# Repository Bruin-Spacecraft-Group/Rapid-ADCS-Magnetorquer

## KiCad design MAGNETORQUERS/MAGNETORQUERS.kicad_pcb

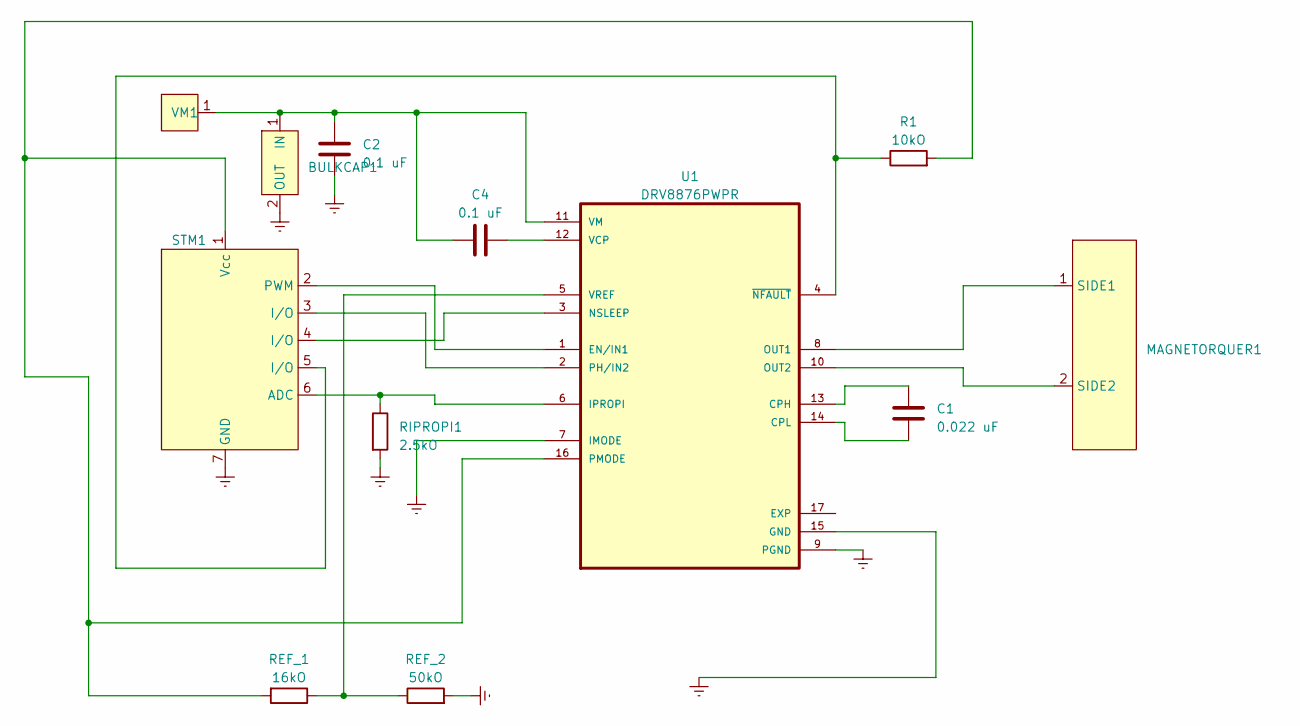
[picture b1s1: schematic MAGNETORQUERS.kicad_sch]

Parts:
BULKCAP1: PinHeader_1x02_P2.54mm_Vertical
C1: 0.022 uF; R_0603_1608Metric
C2, C4: 0.1 uF; R_0603_1608Metric
MAGNETORQUER1: PinHeader_1x02_P2.54mm_Vertical
R1: 10kO; R_0603_1608Metric
REF_1: 16kO; R_0603_1608Metric
REF_2: 50kO; R_0603_1608Metric
RIPROPI1: 2.5kO; R_0603_1608Metric
STM1: PinHeader_1x07_P2.54mm_Vertical
U1: DRV8876PWPR; IC_DRV8876PWPR; PARTREV E
VM1: PinHeader_1x01_P2.54mm_Vertical

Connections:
Earth: BULKCAP1.2 (OUT), C2.2, REF_2.2, RIPROPI1.2, STM1.7 (GND), U1.7 (IMODE), U1.9 (PGND), U1.15 (GND)
unnamed: BULKCAP1.1 (IN), C2.1, C4.1, U1.11 (VM), VM1.1
unnamed: MAGNETORQUER1.1 (SIDE1), U1.8 (OUT1)
unnamed: MAGNETORQUER1.2 (SIDE2), U1.10 (OUT2)
unnamed: RIPROPI1.1, STM1.6 (ADC), U1.6 (IPROPI)
unnamed: STM1.2 (PWM), U1.1 (EN/IN1)
unnamed: R1.2, REF_1.2, STM1.1 (Vcc), U1.16 (PMODE)
unnamed: C1.1, U1.13 (CPH)
unnamed: C1.2, U1.14 (CPL)
unnamed: STM1.4 (I/O), U1.3 (NSLEEP)
unnamed: STM1.3 (I/O), U1.2 (PH/IN2)
unnamed: C4.2, U1.12 (VCP)
unnamed: REF_1.1, REF_2.1, U1.5 (VREF)
unnamed: R1.1, STM1.5 (I/O), U1.4 (~NFAULT)

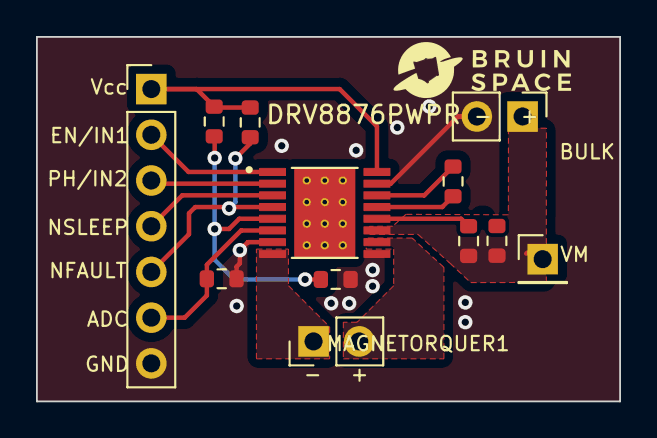
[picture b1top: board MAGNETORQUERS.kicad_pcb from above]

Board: 2 copper layers, 32.4 x 20.2 mm, 12 parts (0 on the bottom side), 14 nets.

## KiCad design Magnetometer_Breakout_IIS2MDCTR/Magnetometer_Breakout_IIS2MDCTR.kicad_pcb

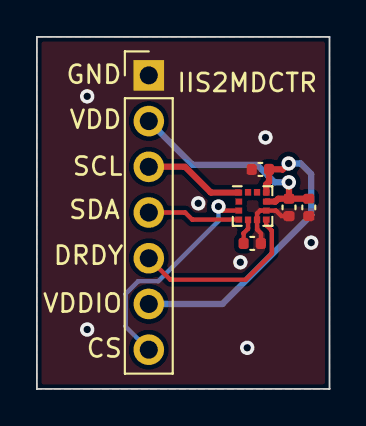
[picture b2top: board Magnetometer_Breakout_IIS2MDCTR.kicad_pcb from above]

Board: 2 copper layers, 16.3 x 19.6 mm, 6 parts (0 on the bottom side), 8 nets.

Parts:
C1: 220nF; C_0402_1005Metric
C2, C4: 100nF; C_0402_1005Metric
C3: 10uF; C_0402_1005Metric
J1: Conn_01x07_Male; PinHeader_1x07_P2.54mm_Vertical
U1: IIS2MDCTR; LGA-12_2x2mm_P0.5mm

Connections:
CS: J1.7, U1.3 (CS)
DRDY: J1.5, U1.7 (INT/DRDY)
GND: C1.2, C2.2, C3.2, C4.2, J1.1, U1.6 (GND), U1.8 (GND)
unnamed: C1.1, U1.5 (C1)
SCL: J1.3, U1.1 (SCL/SPC)
SDA: J1.4, U1.4 (SDA/SDI/SDO)
VDD: C2.1, C3.1, J1.2, U1.9 (VDD)
VDDIO: C4.1, J1.6, U1.10 (VDD_IO)

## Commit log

2023-03-03 created initial programs
2023-03-03 updated stuff
2023-03-06 updated to move back and forth
2023-03-11 created better winder code
2023-03-18 stoofs
2023-03-18 created schematic
2023-04-12 created iis2mdctr pcb
2023-04-12 Mag driver initial commit
2023-04-13 Finished magnetorquer driver ic breakout
2023-04-16 updated stuff seth said was bad
2023-04-25 updated minor stuff
2023-04-25 generated gerber files
2023-04-25 Initial helmholts driver sch
2023-04-25 AHHHHH CONNECTIONS
2023-04-26 fixed wiring, still DRC errors
2023-04-26 fix some schematic drc errors
2023-04-29 ur mom
2023-04-29 more tracks!
2023-05-01 idek what happened
2023-05-01 TRACES
2023-05-07 finalized board
    shrunk board size
    relabeled pwm pin to reflect drv pin name
    moved magnetorquer header pads closer
    got rid of resistor/capacitor silkscreens, too small to see
    edited drv8876 footprint to not have drc errors (increased via sizes, made thermal vias same pad #)
    added more thermal vias on bottom cap directly below drv as recommended by datasheet
2023-05-07 made ground plane not have thermal reliefs
2023-05-07 connected drv middle thermal pad to ground (it wasn't connected to anything)
2023-05-07 gerber files
2023-05-07 wups
2023-05-07 ok these are the gerbers fr this time
2023-05-09 finish bridge footprint
2023-05-13 here
2023-05-14 did pwm
2023-05-15 mag pwm control
2023-05-31 made some code
2023-05-31 idek
2023-06-02 ahhh
2023-08-10 Create file1
2023-08-10 changed MAGNETORQUER to DRV8876PWP
2023-08-10 renamed a few folders and moved IIS2MDCTR back to magnetorquer folder
    renamed IIS2MDCTR pcb and IIS2MDCTR code and put them in same folder
2023-08-10 unsure of mag driver vs DRV
2023-08-17 name changes
2023-08-17 name changes and folder reorganisation
2023-10-24 magnetometer and driver code
2025-01-24 stuff idk
2025-01-24 addedd mag winder 2 code
